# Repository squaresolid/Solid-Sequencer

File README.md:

# Solid-Sequencer
Solid Sequencer, 8 step sequencer based on 4022

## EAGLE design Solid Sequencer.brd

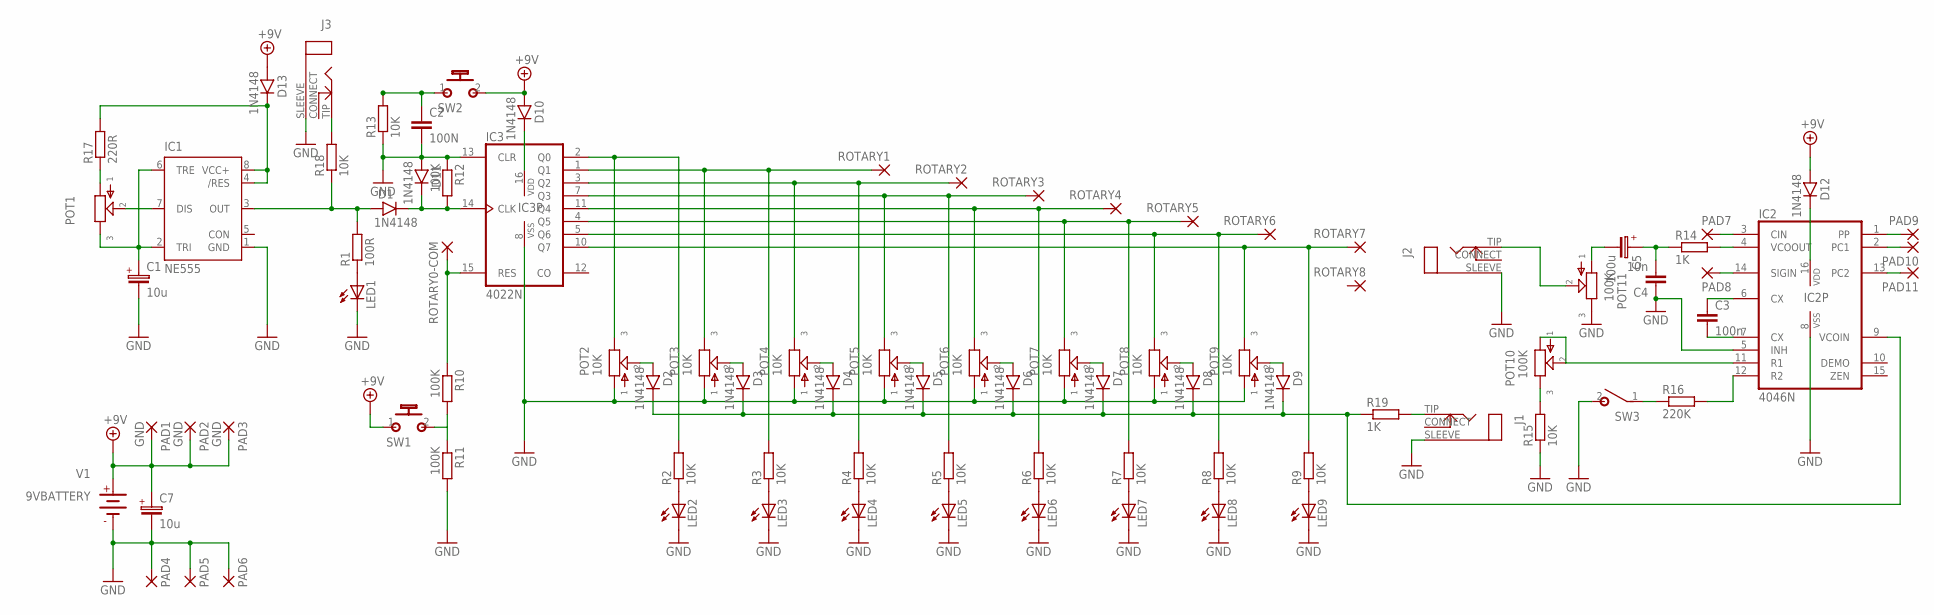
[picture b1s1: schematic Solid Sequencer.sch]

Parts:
C1: 10u; 050_020
C2: 100N; 075X030_3
C3: 100n; 075X030
C4: 10n; 075X030
C5: 100u; 050_020_1
C7: 10u; 050_020_1
D1, D2, D3, D4, D5, D6, D7, D8, D9, D10, D11, D12, D13: 1N4148; DO35-3
IC1: NE555; DIL-08
IC2: 4046N; DIL16
IC3: 4022N; DIL16
J1, J2, J3: CLOSEDMONO; CLOSED_MONO_JACK
LED1, LED2, LED3, LED4, LED5, LED6, LED7, LED8, LED9: LED3MM
PAD1, PAD2, PAD3: GND; 2,15/1,0
PAD4, PAD5, PAD6, PAD7, PAD8, PAD9, PAD10, PAD11: 2,15/1,0
POT1: POT-EU; POT
POT2, POT3, POT4, POT5, POT6, POT7, POT8, POT9: 10K; POT
POT10, POT11: 100K; POT
R1: 100R; 0207/7
R2, R3, R4, R5, R6, R7, R8, R9, R13, R15, R18: 10K; 0207/7
R10, R11, R12: 100K; 0207/7
R14, R19: 1K; 0207/7
R16: 220K; 0207/7
R17: 220R; 0207/7
ROTARY0-COM, ROTARY1, ROTARY2, ROTARY3, ROTARY4, ROTARY5, ROTARY6, ROTARY7, ROTARY8: 2,15/1,0
SW1, SW2: MOMENTARY; SPST
SW3: SPST
V1: 9VBATTERY; AB9V

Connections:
+9V: C7.+, D10.A, D12.A, D13.A, PAD1.1, PAD2.1, PAD3.1, SW1.1, SW2.2 (S), V1.+
GND: C1.-, C2.2, C4.1, C7.-, D11.A, IC1.1 (GND), IC2.5 (INH), IC2.8 (VSS), IC3.8 (VSS), IC3.13 (CLR), J1.SLEEVE (RING), J2.SLEEVE (RING), J3.SLEEVE (RING), LED1.K (C), LED2.K (C), LED3.K (C), LED4.K (C), LED5.K (C), LED6.K (C), LED7.K (C), LED8.K (C), LED9.K (C), PAD4.1, PAD5.1, PAD6.1, POT2.1, POT3.1, POT4.1, POT5.1, POT6.1, POT7.1, POT8.1, POT9.1, POT11.3, R11.2, R12.1, R13.1, R15.1, SW3.2 (S), V1.-
unnamed: IC1.7 (DIS), POT1.2
unnamed: C1.+, IC1.2 (TRI), IC1.6 (TRE), POT1.3
unnamed: J3.TIP, R18.2
unnamed: LED1.A, R1.1
unnamed: J1.TIP, R19.2
unnamed: IC3.2 (Q0), POT2.3, R2.2
unnamed: D1.C, D11.C, IC3.14 (CLK), R12.2
unnamed: D2.A, POT2.2
unnamed: D2.C, D3.C, D4.C, D5.C, D6.C, D7.C, D8.C, D9.C, IC2.9 (VCOIN), R19.1
unnamed: LED2.A, R2.1
unnamed: IC3.1 (Q1), POT3.3, R3.2, ROTARY1.1
unnamed: D3.A, POT3.2
unnamed: D10.C, IC3.16 (VDD)
unnamed: LED3.A, R3.1
unnamed: IC3.3 (Q2), POT4.3, R4.2, ROTARY2.1
unnamed: D4.A, POT4.2
unnamed: IC2.11 (R1), POT10.1, POT10.2
unnamed: LED4.A, R4.1
unnamed: IC3.7 (Q3), POT5.3, R5.2, ROTARY3.1
unnamed: D5.A, POT5.2
unnamed: R10.2, R11.1, SW1.2 (S)
unnamed: LED5.A, R5.1
unnamed: IC3.11 (Q4), POT6.3, R6.2, ROTARY4.1
unnamed: D6.A, POT6.2
unnamed: C2.1, R13.2, SW2.1
unnamed: LED6.A, R6.1
unnamed: IC3.15 (RES), R10.1, ROTARY0-COM.1
unnamed: D7.A, POT7.2
unnamed: D1.A, IC1.3 (OUT), R1.2, R18.1
unnamed: LED7.A, R7.1
unnamed: IC3.5 (Q6), POT8.3, R8.2, ROTARY6.1
unnamed: D8.A, POT8.2
unnamed: LED8.A, R8.1
unnamed: IC3.10 (Q7), POT9.3, R9.2, ROTARY7.1
unnamed: D9.A, POT9.2
unnamed: D12.C, IC2.16 (VDD)
unnamed: LED9.A, R9.1
unnamed: IC2.3 (CIN), PAD7.1
unnamed: C3.1, IC2.6 (CX)
unnamed: C3.2, IC2.7 (CX)
unnamed: IC2.12 (R2), R16.2
unnamed: POT10.3, R15.2
unnamed: IC2.14 (SIGIN), PAD8.1
unnamed: IC2.4 (VCOOUT), R14.2
unnamed: C4.2, C5.+, R14.1
unnamed: C5.-, POT11.1
unnamed: R16.1, SW3.1
unnamed: IC2.1 (PP), PAD9.1
unnamed: IC2.2 (PC1), PAD10.1
unnamed: IC2.13 (PC2), PAD11.1
unnamed: IC3.4 (Q5), POT7.3, R7.2, ROTARY5.1
unnamed: POT1.1, R17.1
unnamed: D13.C, IC1.4 (/RES), IC1.8 (VCC+), R17.2
unnamed: J2.TIP, POT11.2

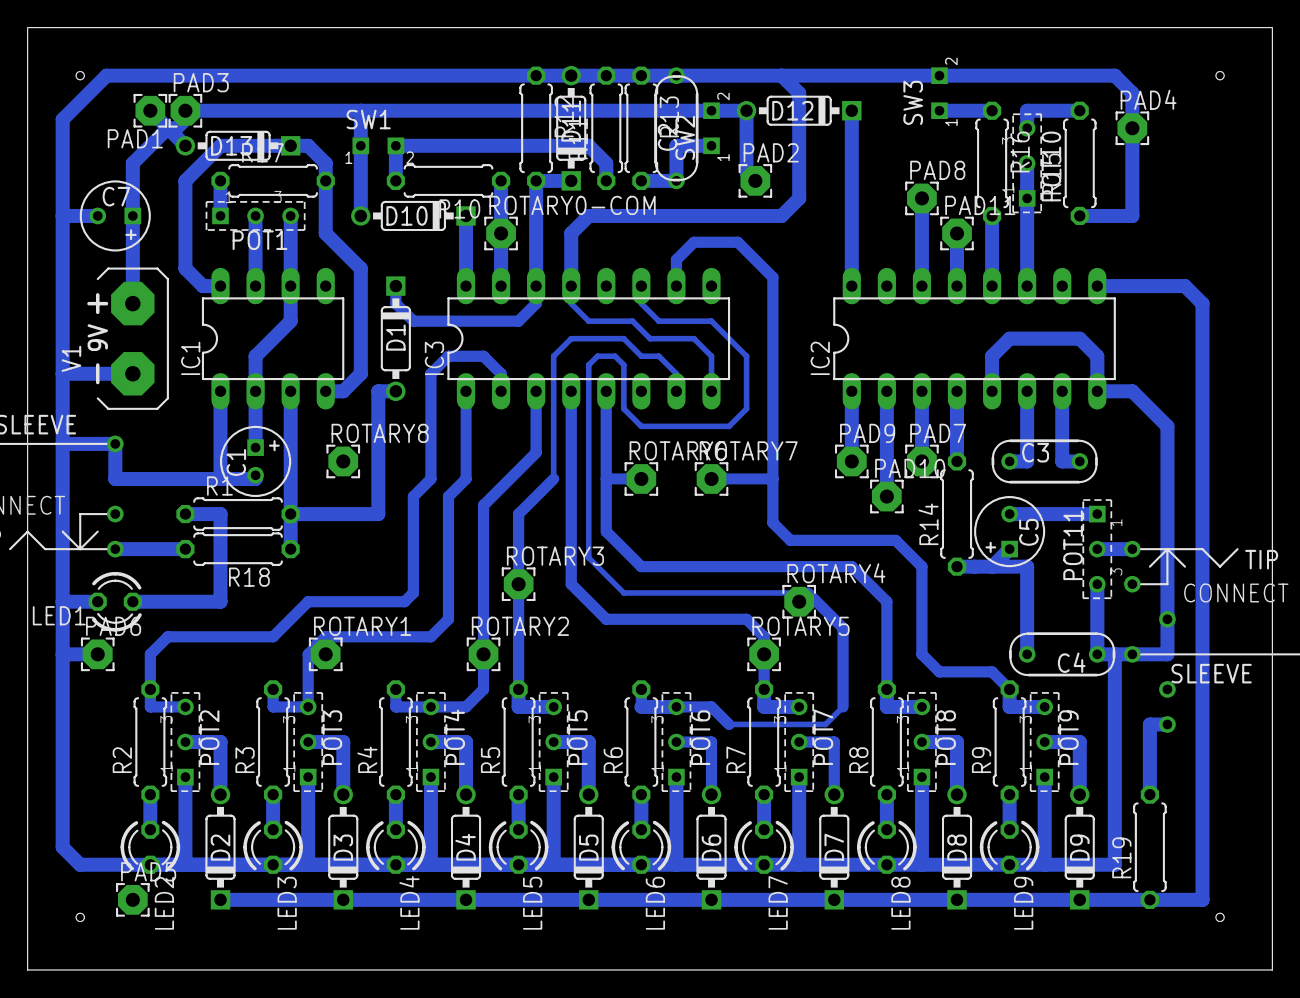
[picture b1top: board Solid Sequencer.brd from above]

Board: 2 copper layers, 90.2 x 68.2 mm, 88 parts (1 on the bottom side), 56 nets.

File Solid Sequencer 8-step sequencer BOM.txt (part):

Partlist

Assembly variant: 

Part        Value          Package          Library               Position (inch)       Orientation

C1          10u            050_020          gm-caps-electro-pol   (0.65 1.45)           R270
C2          100N           075X030_3        gm-caps-film-chicklet (1.85 2.4)            R90
C3          100n           075X030          gm-caps-film-chicklet (2.9 1.45)            R0
C4          10n            075X030          gm-caps-film-chicklet (2.95 0.9)            R180
C5          100u           050_020_1        gm-caps-electro-pol   (2.8 1.25)            R90
C7          10u            050_020_1        gm-caps-electro-pol   (0.15 2.3)            R180
D1          1N4148         DO35-3           gm-diodes             (1.05 1.8)            R270
D2          1N4148         DO35-3           gm-diodes             (0.55 0.35)           R90
D3          1N4148         DO35-3           gm-diodes             (0.9 0.35)            R90
D4          1N4148         DO35-3           gm-diodes             (1.25 0.35)           R90
D5          1N4148         DO35-3           gm-diodes             (1.6 0.35)            R90
D6          1N4148         DO35-3           gm-diodes             (1.95 0.35)           R90
D7          1N4148         DO35-3           gm-diodes             (2.3 0.35)            R90
D8          1N4148         DO35-3           gm-diodes             (2.65 0.35)           R90
D9          1N4148         DO35-3           gm-diodes             (3 0.35)              R90
D11         1N4148         DO35-3           gm-diodes             (1.55 2.4)            R90
D12                        DO41-3           gm-diodes             (0.3 2.15)            R270
IC1         NE555          DIL-08           st-microelectronics   (0.7 1.8)             R0
IC2         4046N          DIL16            40xx                  (2.7 1.8)             R0
IC3         4022N          DIL16            40xx                  (1.6 1.8)             R0
J1                         CLOSED_MONO_JACK gm-jacks              (3.55 0.85)           MR0
J2                         CLOSED_MONO_JACK gm-jacks              (3.45 1.05)           R180
J3                         CLOSED_MONO_JACK gm-jacks              (-0.05 1.35)          R0
LED1                       LED3MM           led                   (0.25 1.05)           R180
LED2                       LED3MM           led                   (0.35 0.35)           R270
LED3                       LED3MM           led                   (0.7 0.35)            R270
LED4                       LED3MM           led                   (1.05 0.35)           R270
LED5                       LED3MM           led                   (1.4 0.35)            R270
LED6                       LED3MM           led                   (1.75 0.35)           R270
LED7                       LED3MM           led                   (2.1 0.35)            R270
LED8                       LED3MM           led                   (2.45 0.35)           R270
LED9                       LED3MM           led                   (2.8 0.35)            R270
PAD1        GND            2,15/1,0         wirepad               (0.35 2.45)           R180
PAD2        GND            2,15/1,0         wirepad               (2.075 2.25)          R0
PAD3        GND            2,15/1,0         wirepad               (0.45 2.45)           R0
PAD4                       2,15/1,0         wirepad               (3.15 2.4)            R0
PAD5                       2,15/1,0         wirepad               (0.3 0.2)             R0
PAD6                       2,15/1,0         wirepad               (0.2 0.9)             R0
PAD7                       2,15/1,0         wirepad               (2.55 1.45)           R0
PAD8                       2,15/1,0         wirepad               (2.55 2.2)            R0
PAD9                       2,15/1,0         wirepad               (2.35 1.45)           R0
PAD10                      2,15/1,0         wirepad               (2.45 1.35)           R0
PAD11                      2,15/1,0         wirepad               (2.65 2.1)            R0
POT1                       POT              gm-pots               (0.65 2.2)            MR0
POT2        10K            POT              gm-pots               (0.45 0.65)           R270
POT3        10K            POT              gm-pots               (0.8 0.65)            R270
POT4        10K            POT              gm-pots               (1.15 0.65)           R270
POT5        10K            POT              gm-pots               (1.5 0.65)            R270
POT6        10K            POT              gm-pots               (1.85 0.65)           R270
POT7        10K            POT              gm-pots               (2.2 0.65)            R270
POT8        10K            POT              gm-pots               (2.55 0.65)           R270
POT9        10K            POT              gm-pots               (2.9 0.65)            R270
POT10       100K           POT              gm-pots               (2.85 2.3)            R270
POT11       100K           POT              gm-pots               (3.05 1.2)            R90
R1          4K7            0207/7           rcl                   (0.6 1.3)             R0
R2          10K            0207/7           rcl                   (0.35 0.65)           R90
R3          10K            0207/7           rcl                   (0.7 0.65)            R90
R4          10K            0207/7           rcl                   (1.05 0.65)           R90
R5          10K            0207/7           rcl                   (1.4 0.65)            R90
R6          10K            0207/7           rcl                   (1.75 0.65)           R90
R7          10K            0207/7           rcl                   (2.1 0.65)            R90
R8          10K            0207/7           rcl                   (2.45 0.65)           R90
R9          10K            0207/7           rcl                   (2.8 0.65)            R90
R10         100K           0207/7           rcl                   (1.2 2.25)            R180
R11         100K           0207/7           rcl                   (1.65 2.4)            R90
R12         100K           0207/7           rcl                   (1.45 2.4)            R270
R13         10K            0207/7           rcl                   (1.75 2.4)            R270
R14         1K             0207/7           rcl                   (2.65 1.3)            R90
R15         10K            0207/7           rcl                   (3 2.3)               R90
R16         220K           0207/7           rcl                   (2.75 2.3)            R270
R17         220R           0207/7           rcl                   (0.7 2.35)            R0
R18         10K            0207/7           rcl                   (0.6 1.2)             R180
R19         1K             0207/7           rcl                   (3.2 0.35)            R90
ROTARY0-COM                2,15/1,0         wirepad               (1.35 2.1)            R0
ROTARY1                    2,15/1,0         wirepad               (0.85 0.9)            R0
ROTARY2                    2,15/1,0         wirepad               (1.3 0.9)             R0
ROTARY3                    2,15/1,0         wirepad               (1.4 1.1)             R0
ROTARY4                    2,15/1,0         wirepad               (2.2 1.05)            R0
ROTARY5                    2,15/1,0         wirepad               (2.1 0.9)             R0
ROTARY6                    2,15/1,0         wirepad               (1.75 1.4)            R0
ROTARY7                    2,15/1,0         wirepad               (1.95 1.3)            R0
ROTARY8                    2,15/1,0         wirepad               (0.9 1.45)            R0
SW1         MOMENTARY      SPST             gm-switches           (1 2.35)              R0
SW2         MOMENTARY      SPST             gm-switches           (1.95 2.4)            R90
SW3         SPST           SPST             gm-switches           (2.6 2.5)             R90
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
